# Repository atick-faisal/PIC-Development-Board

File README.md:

# PIC Development Board  

## PCB Layout (Top and Bottom View)

## License

This work is licensed under [GNU General Public License v3.0](https://github.com/atick-faisal/PIC16F877a/blob/master/LICENSE).

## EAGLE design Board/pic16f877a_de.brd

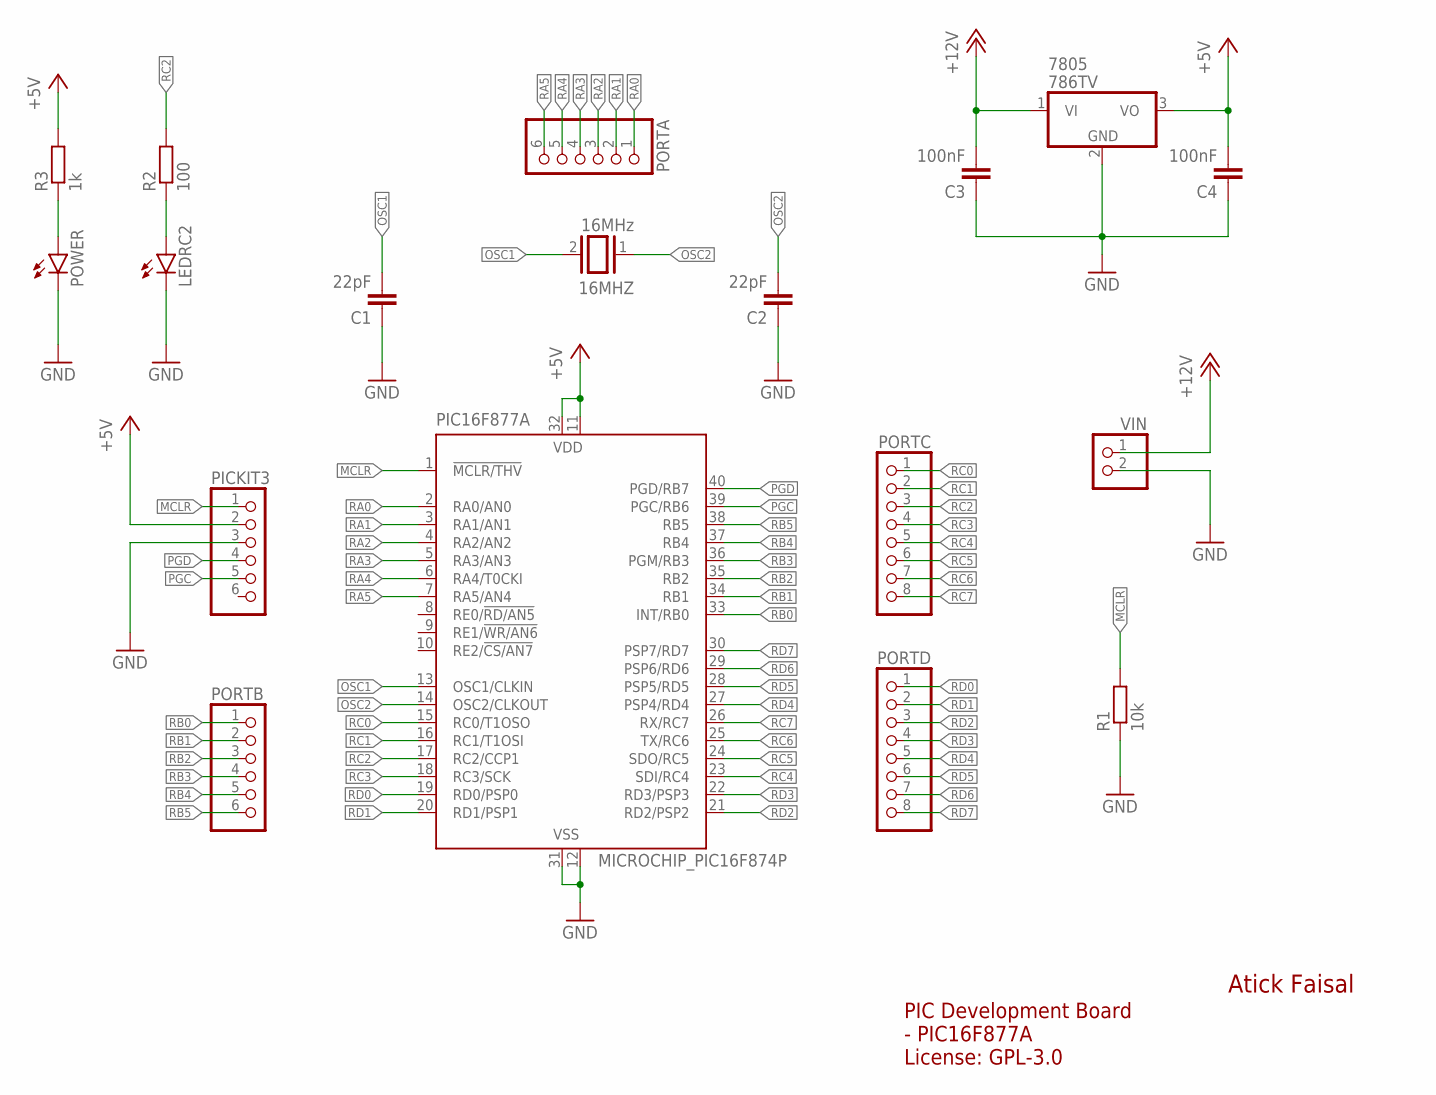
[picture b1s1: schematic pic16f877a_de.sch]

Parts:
16MHZ: 16MHz; QS
7805: 786TV; TO220V
C1, C2: 22pF; C025-025X050
C3, C4: 100nF; C025-025X050
LEDRC2: LED5MM
PIC16F877A: MICROCHIP_PIC16F874P; MICROCHIP_DIL40
PICKIT3: PINHD-1X6; 1X06
PORTA: PINHD-1X6; 1X06
PORTB: PINHD-1X6; 1X06
PORTC: PINHD-1X8; 1X08
PORTD: PINHD-1X8; 1X08
POWER: LED5MM
R1: 10k; 0207/7
R2: 100; 0207/7
R3: 1k; 0207/7
VIN: PINHD-1X2; 1X02

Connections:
+5V: 7805.3 (VO), C4.2, PIC16F877A.11 (VDD), PIC16F877A.32 (VDD), PICKIT3.2, R3.2
+12V: 7805.1 (VI), C3.2, VIN.1
GND: 7805.2 (GND), C1.1, C2.1, C3.1, C4.1, LEDRC2.K (C), PIC16F877A.12 (VSS), PIC16F877A.31 (VSS), PICKIT3.3, POWER.K (C), R1.1, VIN.2
MCLR: PIC16F877A.1 (!MCLR/THV), PICKIT3.1, R1.2
unnamed: POWER.A, R3.1
unnamed: LEDRC2.A, R2.1
OSC1: 16MHZ.2, C1.2, PIC16F877A.13 (OSC1/CLKIN)
OSC2: 16MHZ.1, C2.2, PIC16F877A.14 (OSC2/CLKOUT)
PGC: PIC16F877A.39 (PGC/RB6), PICKIT3.5
PGD: PIC16F877A.40 (PGD/RB7), PICKIT3.4
RA0: PIC16F877A.2 (RA0/AN0), PORTA.1
RA1: PIC16F877A.3 (RA1/AN1), PORTA.2
RA2: PIC16F877A.4 (RA2/AN2), PORTA.3
RA3: PIC16F877A.5 (RA3/AN3), PORTA.4
RA4: PIC16F877A.6 (RA4/T0CKI), PORTA.5
RA5: PIC16F877A.7 (RA5/AN4), PORTA.6
RB0: PIC16F877A.33 (INT/RB0), PORTB.1
RB1: PIC16F877A.34 (RB1), PORTB.2
RB2: PIC16F877A.35 (RB2), PORTB.3
RB3: PIC16F877A.36 (PGM/RB3), PORTB.4
RB4: PIC16F877A.37 (RB4), PORTB.5
RB5: PIC16F877A.38 (RB5), PORTB.6
RC0: PIC16F877A.15 (RC0/T1OSO), PORTC.1
RC1: PIC16F877A.16 (RC1/T1OSI), PORTC.2
RC2: PIC16F877A.17 (RC2/CCP1), PORTC.3, R2.2
RC3: PIC16F877A.18 (RC3/SCK), PORTC.4
RC4: PIC16F877A.23 (SDI/RC4), PORTC.5
RC5: PIC16F877A.24 (SDO/RC5), PORTC.6
RC6: PIC16F877A.25 (TX/RC6), PORTC.7
RC7: PIC16F877A.26 (RX/RC7), PORTC.8
RD0: PIC16F877A.19 (RD0/PSP0), PORTD.1
RD1: PIC16F877A.20 (RD1/PSP1), PORTD.2
RD2: PIC16F877A.21 (RD2/PSP2), PORTD.3
RD3: PIC16F877A.22 (RD3/PSP3), PORTD.4
RD4: PIC16F877A.27 (PSP4/RD4), PORTD.5
RD5: PIC16F877A.28 (PSP5/RD5), PORTD.6
RD6: PIC16F877A.29 (PSP6/RD6), PORTD.7
RD7: PIC16F877A.30 (PSP7/RD7), PORTD.8

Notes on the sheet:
Atick Faisal
PIC Development Board - PIC16F877A License: GPL-3.0

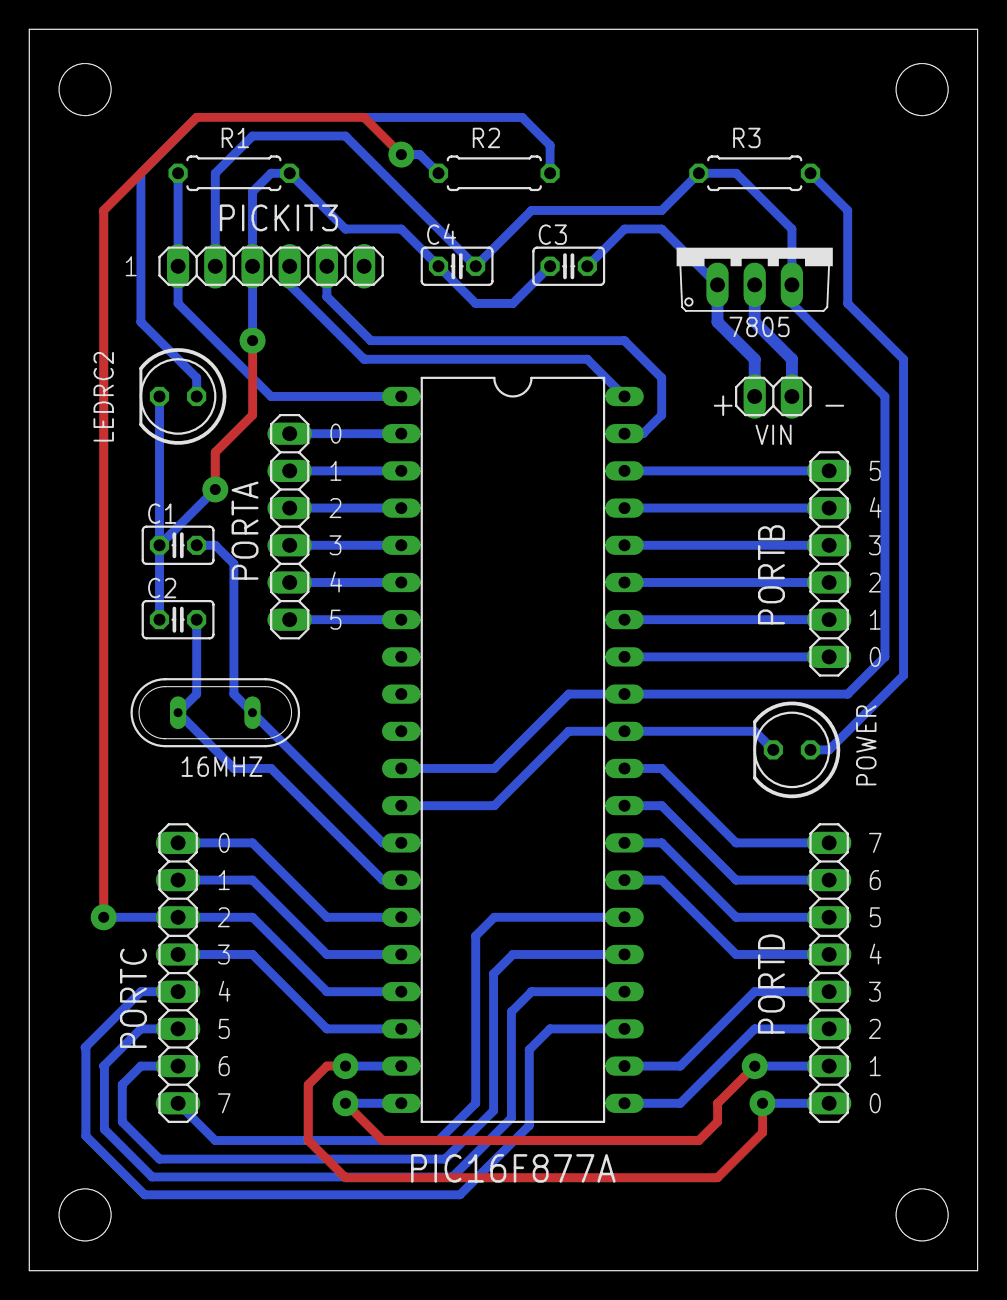
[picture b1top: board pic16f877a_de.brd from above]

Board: 2 copper layers, 64.8 x 84.8 mm, 18 parts (0 on the bottom side), 38 nets.

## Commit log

2019-04-05 Update README.md
    initial commit
2019-04-05 Create LICENSE
2019-04-06 Update README.md
    added icon
2019-05-22 modified

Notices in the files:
README.md:
GPL Licence
